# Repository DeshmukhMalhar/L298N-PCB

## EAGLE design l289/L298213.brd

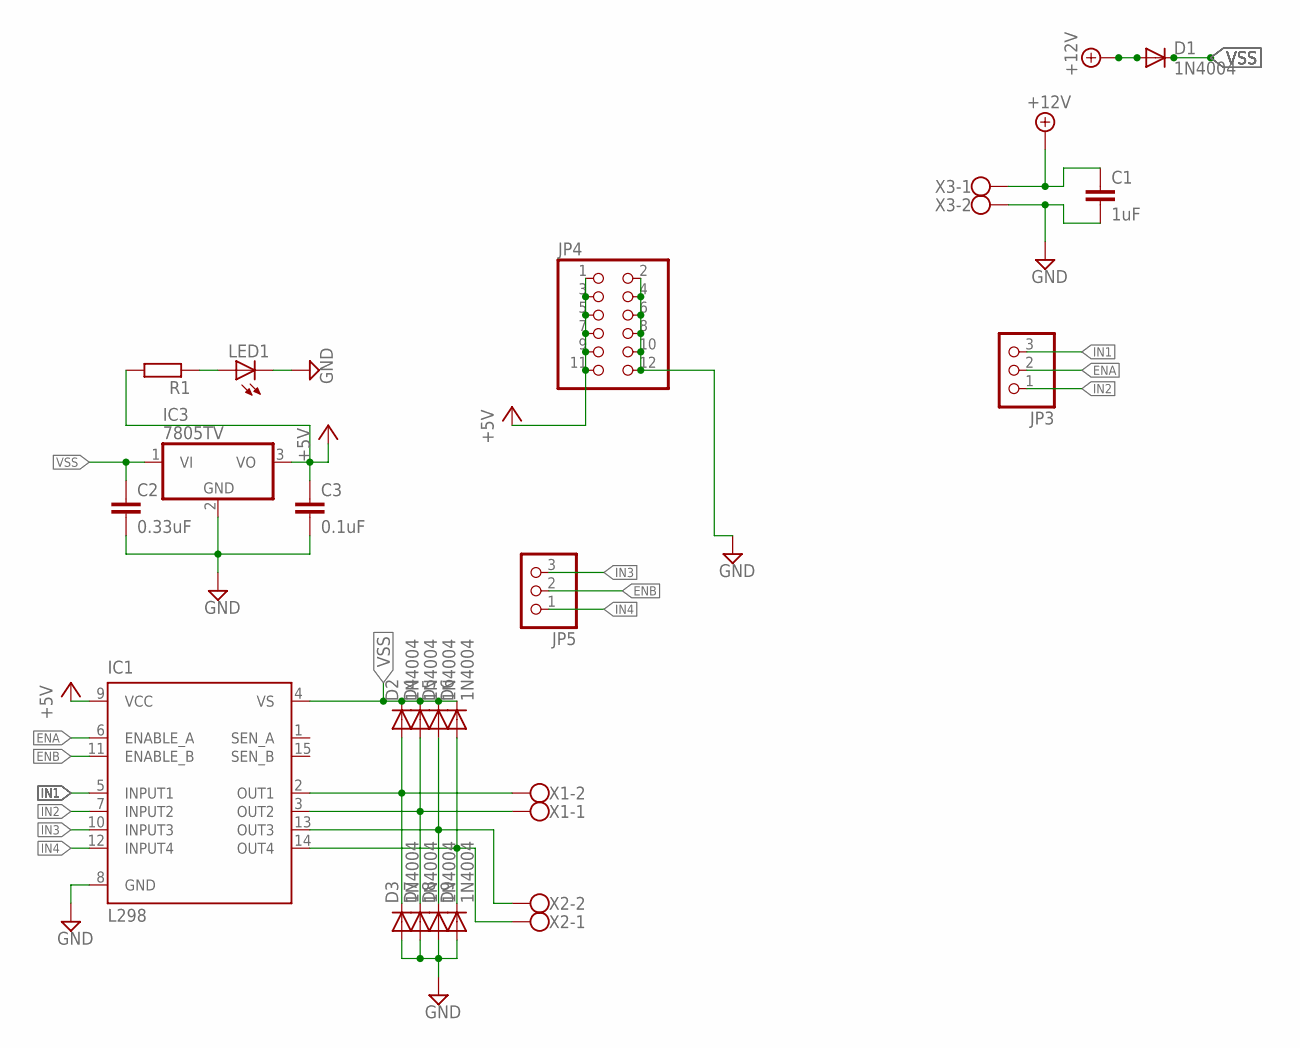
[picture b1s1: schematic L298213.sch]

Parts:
C1: 1uF; C050-024X044
C2: 0.33uF; C050-024X044
C3: 0.1uF; C050-024X044
D1, D2, D3, D4, D5, D6, D7, D8, D9: 1N4004; DO41-10
IC1: L298; MULTIWATT-15
IC3: 7805TV; TO220V
JP3, JP5: PINHD-1X3; 1X03
JP4: PINHD-2X6; 2X06
LED1: LED3MM
R1: R-EU_0207/5V; 0207/5V
X1, X2, X3: W237-102

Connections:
+5V: C3.1, IC1.9 (VCC), IC3.3 (VO), JP4.1, JP4.3, JP4.5, JP4.7, JP4.9, JP4.11, R1.2
+12V: C1.1, D1.A, X3.1
ENA: IC1.6 (ENABLE_A), JP3.2
ENB: IC1.11 (ENABLE_B), JP5.2
GND: C1.2, C2.2, C3.2, D3.A, D7.A, D8.A, D9.A, IC1.8 (GND), IC3.2 (GND), JP4.2, JP4.4, JP4.6, JP4.8, JP4.10, JP4.12, LED1.K (C), X3.2
IN1: IC1.5 (INPUT1), JP3.3
IN2: IC1.7 (INPUT2), JP3.1
IN3: IC1.10 (INPUT3), JP5.3
IN4: IC1.12 (INPUT4), JP5.1
unnamed: D2.A, D3.C, IC1.2 (OUT1), X1.2
unnamed: D4.A, D7.C, IC1.3 (OUT2), X1.1
unnamed: D5.A, D8.C, IC1.13 (OUT3), X2.2
unnamed: D6.A, D9.C, IC1.14 (OUT4), X2.1
unnamed: LED1.A, R1.1
VSS: C2.1, D1.C, D2.C, D4.C, D5.C, D6.C, IC1.4 (VS), IC3.1 (VI)

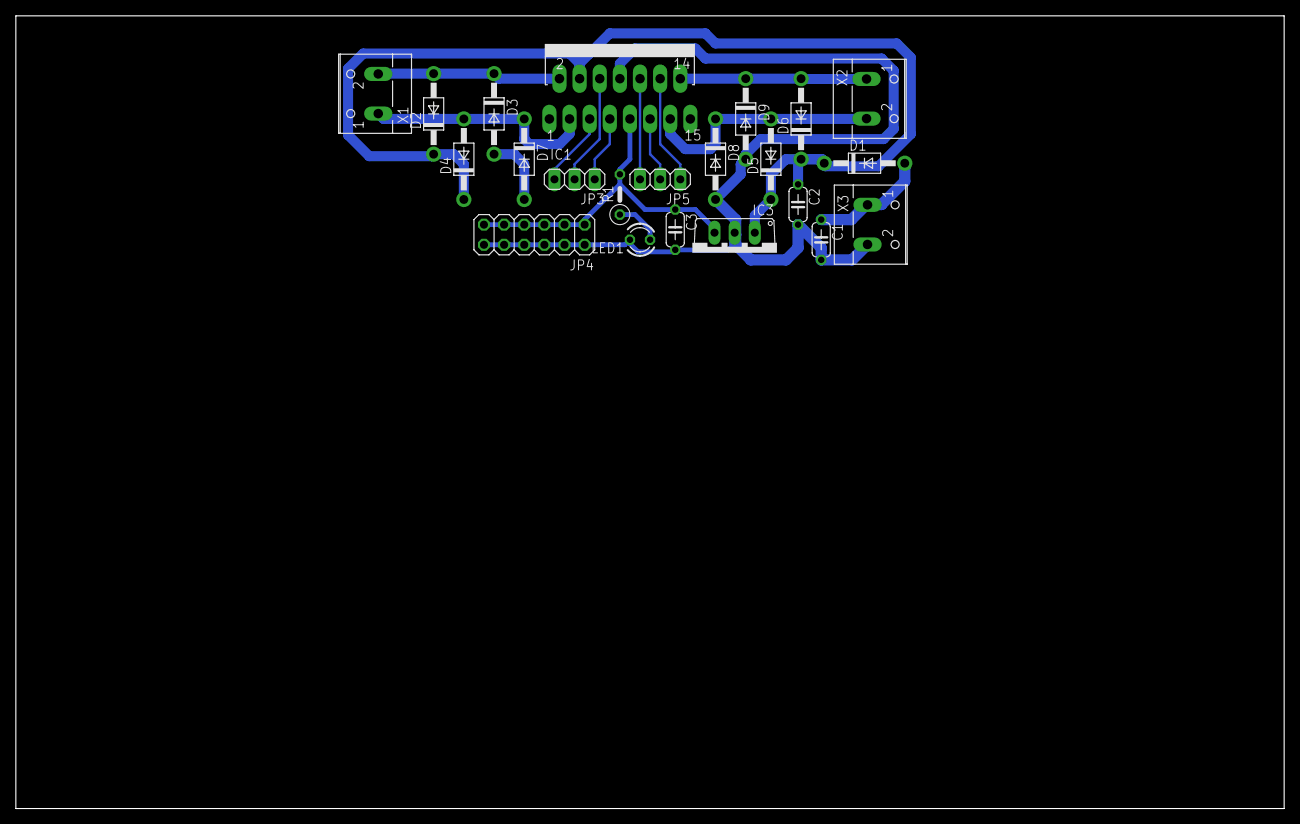
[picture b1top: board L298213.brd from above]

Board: 2 copper layers, 160.0 x 100.0 mm, 22 parts (0 on the bottom side), 15 nets.

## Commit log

2017-08-28 first version
2017-08-28 second version
2017-08-28 Changed Screw terminal footprint
2017-08-28 Added frame in SCH
2017-08-28 Routed halfway through
2017-08-29 Routed the board completely
